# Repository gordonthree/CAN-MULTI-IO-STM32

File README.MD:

# Analog / Digital Multi-IO Controller STM32
Compact module intended to interface with various analog and digital sensor modules, as well as provide generic digital outputs. An isolated CAN interface provides expansion capability with other modules, displays and sensors.

# Multi-IO Node
* STM32G0B1RCT Microcontroller; 64mhz clock, 256k flash, 144k ram
* Automotive grade switch-mode power supply for 5v rail
* Automotive grade low-dropout linear supply for 3.3v rail
* 3-pin terminal block for CAN bus connection with drain
* Jumper selected CAN terminator resistor
* Analog header with four 16-bit ADC inputs
* GPIO header with four digital input/outputs
* Dedicated external I2C bus with interface buffer (hot swap capable)
* One-Wire bus header (USART1-TX)
* Two LED indicators for status, controlled by the micro
* Power input transient voltage protection diode for harsh environments
* Voltage divider to monitor input voltage
* Headers for USART3 serial port and the SWLINK programming connector

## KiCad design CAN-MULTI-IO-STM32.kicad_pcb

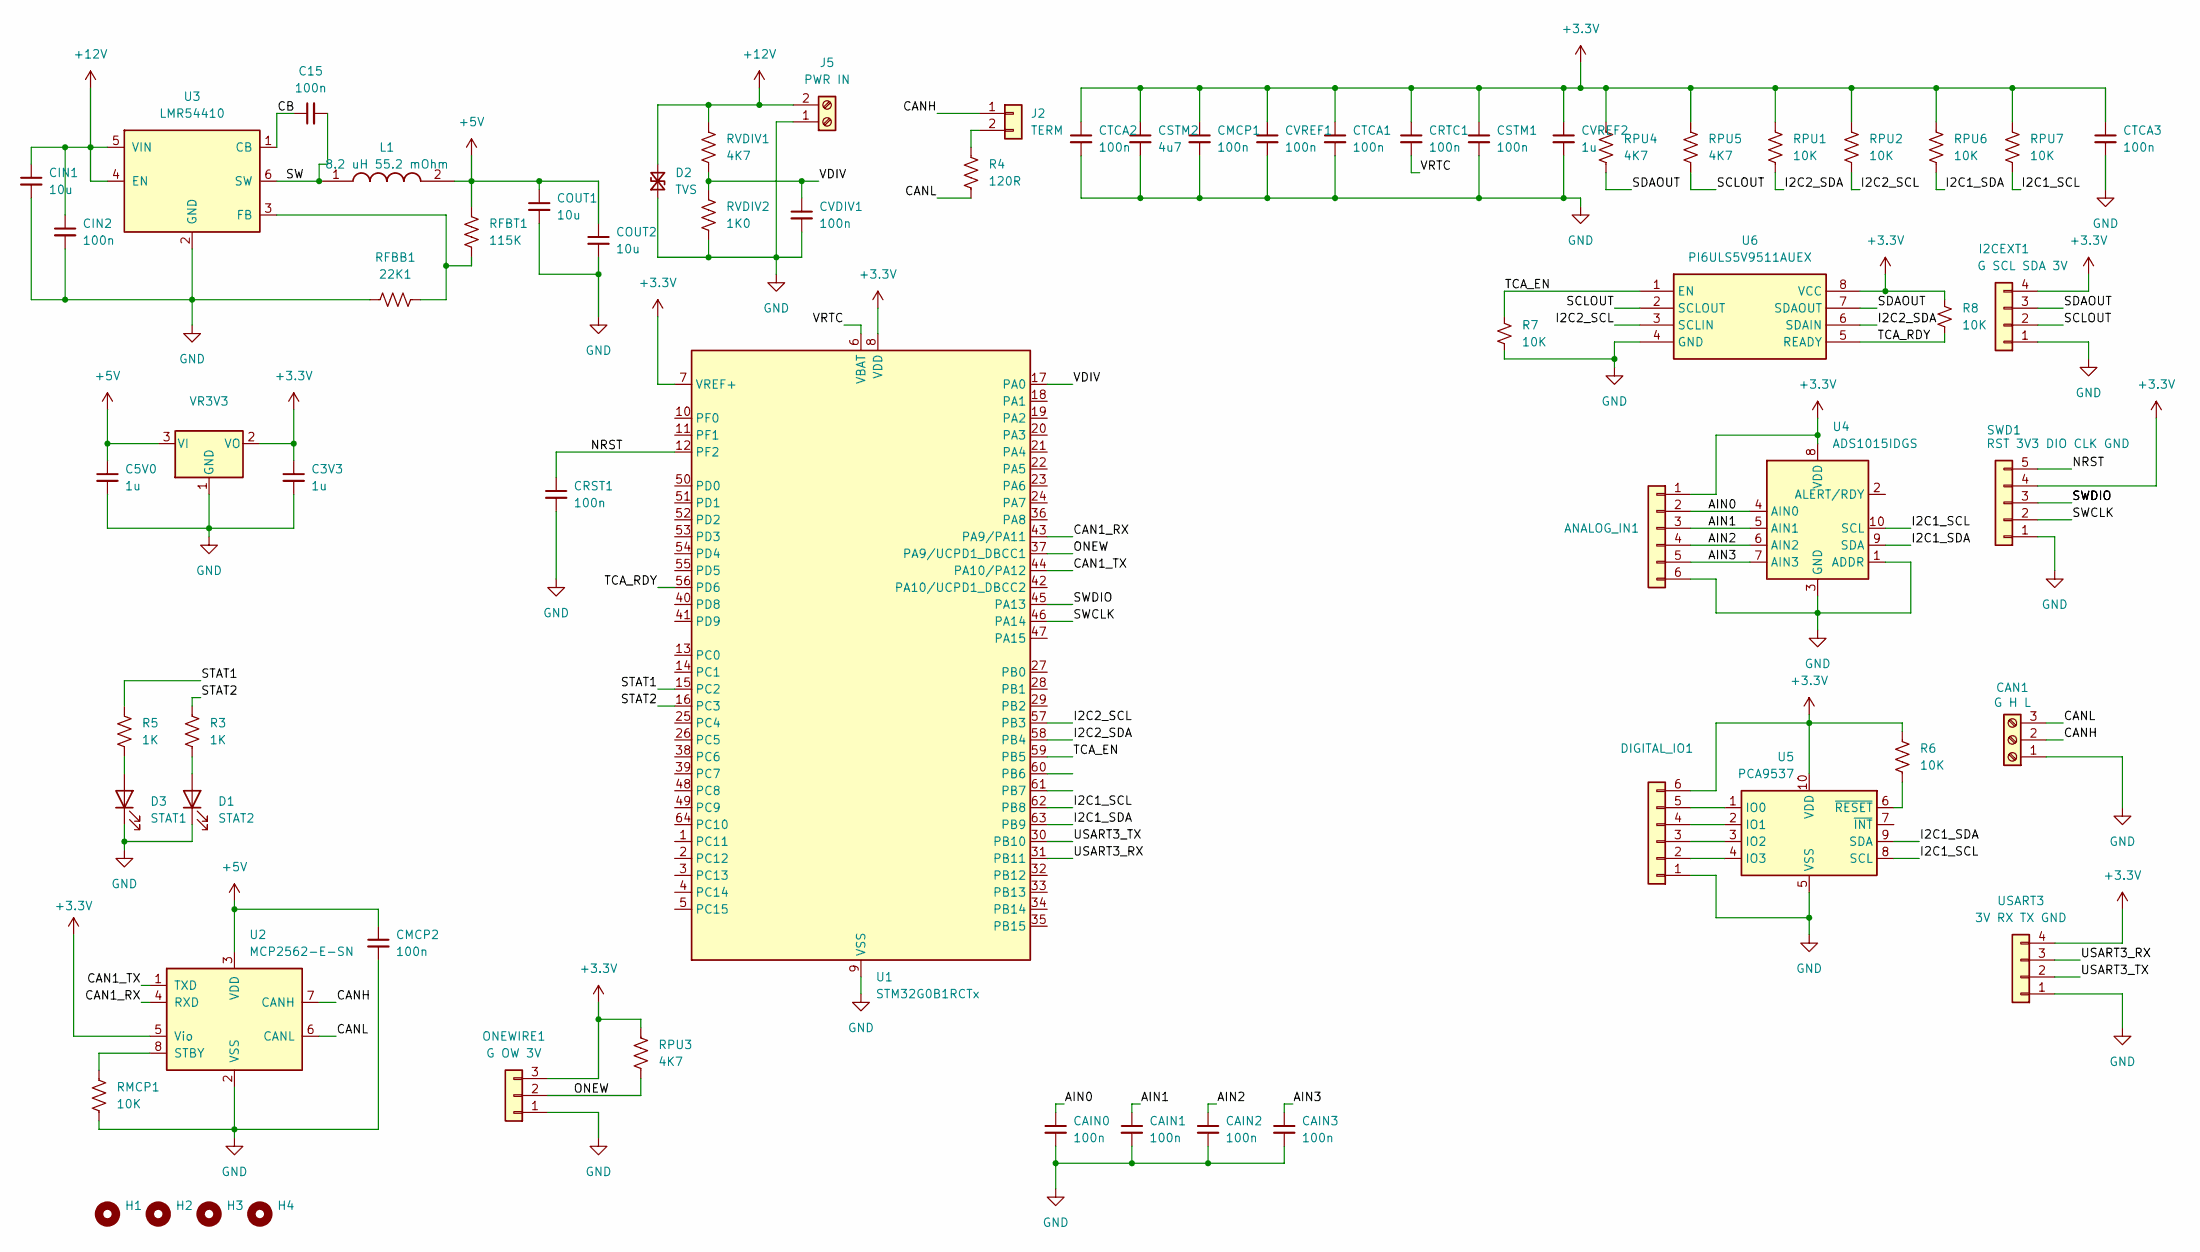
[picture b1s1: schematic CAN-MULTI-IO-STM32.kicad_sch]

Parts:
ANALOG_IN1: 1725698; TerminalBlock_Phoenix_MPT-0,5-6-2.54_1x06_P2.54mm_Horizontal
C3V3, C5V0: 1u; C_0805_2012Metric_Pad1.18x1.45mm_HandSolder
C15: 100n; C_0603_1608Metric_Pad1.08x0.95mm_HandSolder
CAIN0, CAIN1, CAIN2, CAIN3: 100n; C_0603_1608Metric_Pad1.08x0.95mm_HandSolder
CAN1: G H L; TerminalBlock_Phoenix_MPT-0,5-3-2.54_1x03_P2.54mm_Horizontal
CIN1: 10u; C_1210_3225Metric_Pad1.33x2.70mm_HandSolder
CIN2: 100n; C_0603_1608Metric_Pad1.08x0.95mm_HandSolder
CMCP1, CMCP2: 100n; C_0603_1608Metric_Pad1.08x0.95mm_HandSolder
COUT1, COUT2: 10u; C_0805_2012Metric_Pad1.18x1.45mm_HandSolder
CRST1: 100n; C_0603_1608Metric_Pad1.08x0.95mm_HandSolder
CRTC1: 100n; C_0603_1608Metric_Pad1.08x0.95mm_HandSolder
CSTM1: 100n; C_0603_1608Metric_Pad1.08x0.95mm_HandSolder
CSTM2: 4u7; C_0805_2012Metric_Pad1.18x1.45mm_HandSolder
CTCA1, CTCA2, CTCA3: 100n; C_0603_1608Metric_Pad1.08x0.95mm_HandSolder
CVDIV1: 100n; C_0603_1608Metric_Pad1.08x0.95mm_HandSolder
CVREF1: 100n; C_0603_1608Metric_Pad1.08x0.95mm_HandSolder
CVREF2: 1u; C_0603_1608Metric_Pad1.08x0.95mm_HandSolder
D1: STAT2; LED_0805_2012Metric_Pad1.15x1.40mm_HandSolder
D2: TVS; D_SMA_Handsoldering
D3: STAT1; LED_0805_2012Metric_Pad1.15x1.40mm_HandSolder
DIGITAL_IO1: 1725698; TerminalBlock_Phoenix_MPT-0,5-6-2.54_1x06_P2.54mm_Horizontal
H1, H2, H3, H4: MountingHole; MountingHole_3.2mm_M3_DIN965
I2CEXT1: G SCL SDA 3V; PinHeader_1x04_P2.54mm_Horizontal
J2: TERM; PinHeader_1x02_P2.54mm_Vertical
J5: PWR IN; TerminalBlock_Phoenix_MKDS-1,5-2_1x02_P5.00mm_Horizontal
L1: 8.2 uH 55.2 mOhm; SRP5030HMT2R2M; Mouser Part Number SRP5030HMT-8R2M
ONEWIRE1: G OW 3V; PinHeader_1x03_P2.54mm_Horizontal
R3, R5: 1K; R_0603_1608Metric_Pad0.98x0.95mm_HandSolder
R4: 120R; R_Axial_DIN0207_L6.3mm_D2.5mm_P7.62mm_Horizontal
R6, R7, R8: 10K; R_0603_1608Metric_Pad0.98x0.95mm_HandSolder
RFBB1: 22K1; R_0603_1608Metric_Pad0.98x0.95mm_HandSolder
RFBT1: 115K; R_0603_1608Metric_Pad0.98x0.95mm_HandSolder
RMCP1: 10K; R_0603_1608Metric_Pad0.98x0.95mm_HandSolder
RPU1, RPU2, RPU6, RPU7: 10K; R_0603_1608Metric_Pad0.98x0.95mm_HandSolder
RPU3, RPU4, RPU5: 4K7; R_0603_1608Metric_Pad0.98x0.95mm_HandSolder
RVDIV1: 4K7; R_0603_1608Metric_Pad0.98x0.95mm_HandSolder
RVDIV2: 1K0; R_0603_1608Metric_Pad0.98x0.95mm_HandSolder
SWD1: RST 3V3 DIO CLK GND; PinHeader_1x05_P2.54mm_Vertical
U1: STM32G0B1RCTx; LQFP-64_10x10mm_P0.5mm
U2: MCP2562-E-SN; SOIC-8_3.9x4.9mm_P1.27mm
U3: LMR54410; SOT-23-6
U4: ADS1015IDGS; TSSOP-10_3x3mm_P0.5mm
U5: PCA9537; TSSOP-10_3x3mm_P0.5mm
U6: PI6ULS5V9511AUEX; MSOP-8_3x3mm_P0.65mm
USART3: 3V RX TX GND; PinHeader_1x04_P2.54mm_Vertical
VR3V3: TLV1117-33; SOT-223-3_TabPin2

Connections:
+3.3V: ANALOG_IN1.1, C3V3.1, CMCP1.1, CRTC1.1, CSTM1.1, CSTM2.1, CTCA1.1, CTCA2.1, CTCA3.1, CVREF1.1, CVREF2.1, DIGITAL_IO1.6, I2CEXT1.4, ONEWIRE1.3, R6.1, R8.1, RPU1.2, RPU2.2, RPU3.2, RPU4.2, RPU5.2, RPU6.2, RPU7.2, SWD1.4, U1.7 (VREF+), U1.8 (VDD), U2.5 (Vio), U4.8 (VDD), U5.10 (VDD), U6.8 (VCC), USART3.4, VR3V3.2 (VO)
+5V: C5V0.1, CMCP2.1, COUT1.1, COUT2.1, L1.2, RFBT1.1, U2.3 (VDD), VR3V3.3 (VI)
+12V: CIN1.1, CIN2.1, D2.2 (A2), J5.2, RVDIV1.1, U3.4 (EN), U3.5 (VIN)
/AIN0: ANALOG_IN1.2, CAIN0.1, U4.4 (AIN0)
/AIN1: ANALOG_IN1.3, CAIN1.1, U4.5 (AIN1)
/AIN2: ANALOG_IN1.4, CAIN2.1, U4.6 (AIN2)
/AIN3: ANALOG_IN1.5, CAIN3.1, U4.7 (AIN3)
/CAN1_RX: U1.43 (PA9/PA11), U2.4 (RXD)
/CAN1_TX: U1.44 (PA10/PA12), U2.1 (TXD)
/CANH: CAN1.2, J2.1, U2.7 (CANH)
/CANL: CAN1.3, R4.2, U2.6 (CANL)
/CB: C15.1, U3.1 (CB)
/I2C1_SCL: RPU7.1, U1.62 (PB8), U4.10 (SCL), U5.8 (SCL)
/I2C1_SDA: RPU6.1, U1.63 (PB9), U4.9 (SDA), U5.9 (SDA)
/I2C2_SCL: RPU2.1, U1.57 (PB3), U6.3 (SCLIN)
/I2C2_SDA: RPU1.1, U1.58 (PB4), U6.6 (SDAIN)
/NRST: CRST1.1, SWD1.5, U1.12 (PF2)
/ONEW: ONEWIRE1.2, RPU3.1, U1.37 (PA9/UCPD1_DBCC1)
/SCLOUT: I2CEXT1.2, RPU5.1, U6.2 (SCLOUT)
/SDAOUT: I2CEXT1.3, RPU4.1, U6.7 (SDAOUT)
/STAT1: R5.2, U1.15 (PC2)
/STAT2: R3.2, U1.16 (PC3)
/SW: C15.2, L1.1, U3.6 (SW)
/SWCLK: SWD1.2, U1.46 (PA14)
/SWDIO: SWD1.3, U1.45 (PA13)
/TCA_EN: R7.1, U1.59 (PB5), U6.1 (EN)
/TCA_RDY: R8.2, U1.56 (PD6), U6.5 (READY)
/USART3_RX: U1.31 (PB11), USART3.3
/USART3_TX: U1.30 (PB10), USART3.2
/VDIV: CVDIV1.1, RVDIV1.2, RVDIV2.1, U1.17 (PA0)
/VRTC: CRTC1.2, U1.6 (VBAT)
GND: ANALOG_IN1.6, C3V3.2, C5V0.2, CAIN0.2, CAIN1.2, CAIN2.2, CAIN3.2, CAN1.1, CIN1.2, CIN2.2, CMCP1.2, CMCP2.2, COUT1.2, COUT2.2, CRST1.2, CSTM1.2, CSTM2.2, CTCA1.2, CTCA2.2, CTCA3.2, CVDIV1.2, CVREF1.2, CVREF2.2, D1.1 (K), D2.1 (A1), D3.1 (K), DIGITAL_IO1.1, I2CEXT1.1, J5.1, ONEWIRE1.1, R7.2, RFBB1.1, RMCP1.2, RVDIV2.2, SWD1.1, U1.9 (VSS), U2.2 (VSS), U3.2 (GND), U4.1 (ADDR), U4.3 (GND), U5.5 (VSS), U6.4 (GND), USART3.1, VR3V3.1 (GND)
unnamed: D1.2 (A), R3.1
unnamed: D3.2 (A), R5.1
unnamed: DIGITAL_IO1.2, U5.4 (IO3)
unnamed: DIGITAL_IO1.3, U5.3 (IO2)
unnamed: DIGITAL_IO1.4, U5.2 (IO1)
unnamed: DIGITAL_IO1.5, U5.1 (IO0)
unnamed: J2.2, R4.1
unnamed: RMCP1.1, U2.8 (STBY)
unnamed: RFBB1.2, RFBT1.2, U3.3 (FB)
unnamed: R6.2, U5.6 (~RESET)

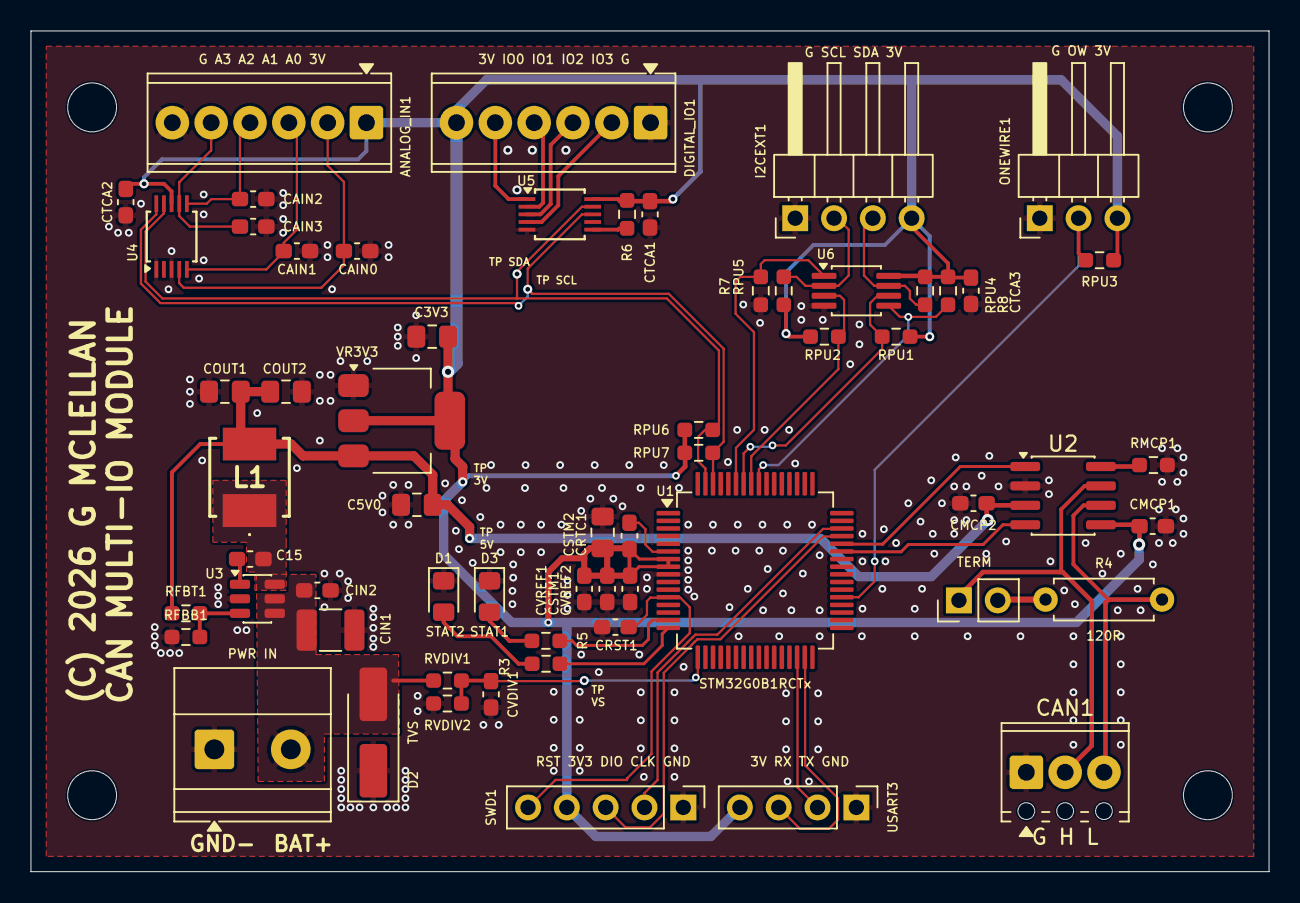
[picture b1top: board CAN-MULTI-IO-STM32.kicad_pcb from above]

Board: 2 copper layers, 81.0 x 55.0 mm, 65 parts (0 on the bottom side), 42 nets.

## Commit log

2026-01-18 added 3d rendering
2026-01-18 schematic and layout refinement
2026-01-18 update url for embedded image
2026-01-18 final tweaks
2026-01-20 major rework to include SMPS and better analog input configuration
2026-01-20 optimized some connectors, switched to SMPS for 5v supply rail
2026-01-20 updated features
2026-01-21 added i2c adc and gpio chips to isolate the mcu, lots of layout work
2026-01-21 lots of progress, lots to do
2026-01-21 first pass layout complete
2026-01-21 updated rendering
2026-01-21 fixed issue with incorrect inductor
2026-01-21 silkscreen cleanup
2026-01-21 refine some details
2026-01-21 fix 2.54mm terminal block issues
2026-01-21 fix a few footprint and drc issues
2026-01-21 update features list
2026-01-21 rename gpio header
2026-01-21 relabel gpio header
2026-01-21 rename image
2026-01-21 update embedded image link
2026-01-21 DRC is clean no errors
2026-01-26 switch to STM32G0B1 micro, refactor pcb layout
2026-01-26 final commit for tonight
2026-01-26 updated 3d rendering
2026-01-26 added ground stitching, silkscreen tweaks, refined 3v supply for STM

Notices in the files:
CAN-MULTI-IO-STM32.kicad_pcb:
(C) 2026 G MCLELLAN
